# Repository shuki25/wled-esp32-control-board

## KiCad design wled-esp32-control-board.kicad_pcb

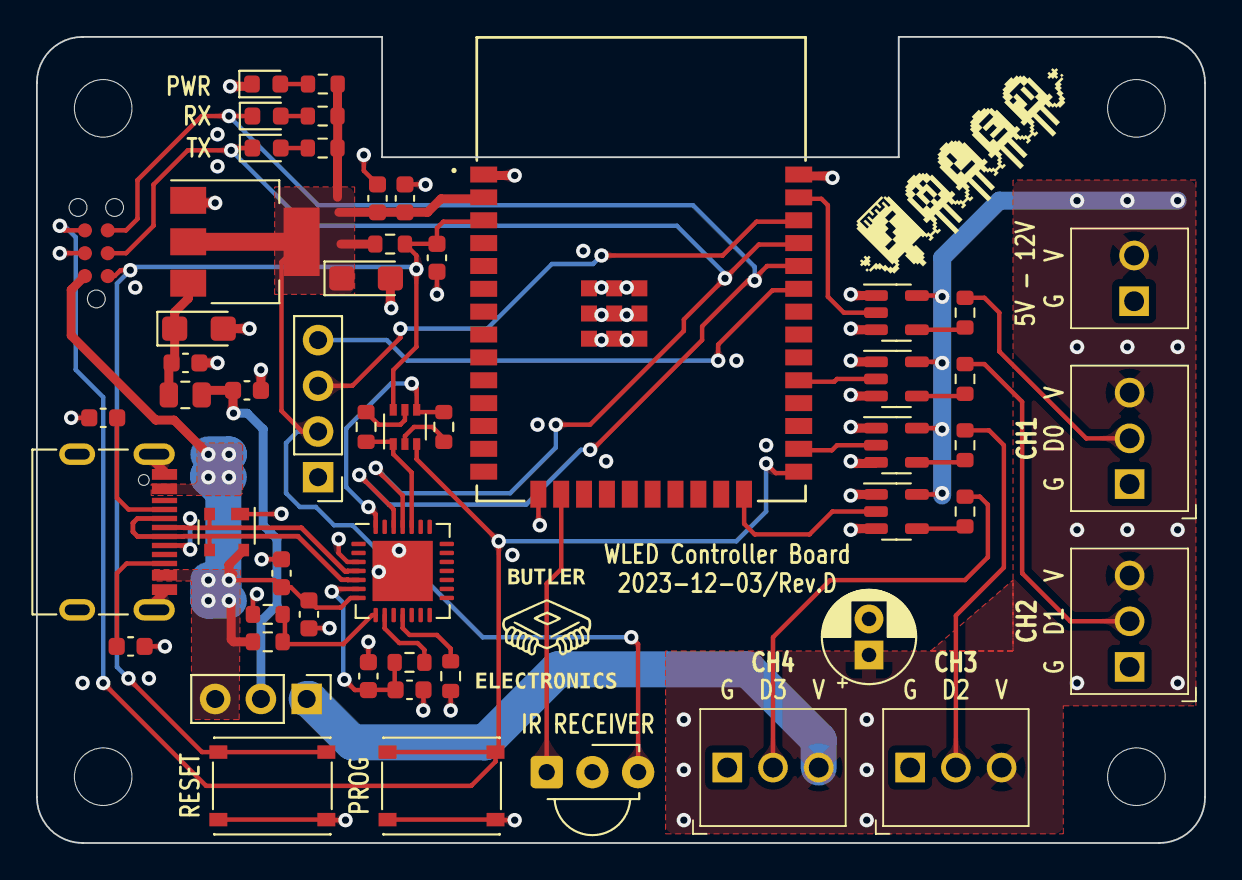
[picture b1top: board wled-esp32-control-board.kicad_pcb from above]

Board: 4 copper layers, 64.9 x 44.8 mm, 57 parts (0 on the bottom side), 40 nets.

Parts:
C101: 22uF; C_0603_1608Metric
C102, C104, C304, C401, C404: 100nF; C_0603_1608Metric
C103: 100uF; CP_Radial_D5.0mm_P2.00mm
C301, C302: 10uF; CP_EIA-3216-10_Kemet-I
C303: 10uF; C_0603_1608Metric
C402, C403: 4.7uF; C_0603_1608Metric
D201: SP0503BAHT; SOT-143
FB301: FerriteBead_Small; R_0805_2012Metric
H101, H102, H103, H104: MountingHole; MountingHole_3.2mm_M3
J101, J102, J103, J104: Conn_01x03; molex-39773-0003
J105: Conn_02x03_Odd_Even; TC2030-IDC-NL
J106: Screw_Terminal_01x02; 397730002
J201: USB_C_Receptacle_USB2.0; USB_C_Receptable_918-418K2023S40001
LED101: BLUE; LED_0603_1608Metric
LED102: GREEN; LED_0603_1608Metric
LED103: RED; LED_0603_1608Metric
OLED101: OLED_I2C; OLED_128x32_I2C_4pins
Q401: MMDT3904; SOT-363_SC-70-6
R101, R402, R405, R408: 10K; R_0603_1608Metric
R102, R103, R106, R108: 100; R_0603_1608Metric
R104, R105, R107: 2K; R_0603_1608Metric
R201, R202: 5K1; C_0603_1608Metric
R401: 1K; R_0603_1608Metric
R403: 22K1; R_0603_1608Metric
R404: 47K5; R_0603_1608Metric
SW101: SW_SPDT; PinHeader_1x03_P2.54mm_Vertical
SW103, SW105: SW_Push; XKB-Connectivity-TS-1187A-B-A-B
U101, U102, U104, U105: 74AHCT1G125; SOT-23-5
U103: ESP32-WROOM-32; ESP32­-WROOM­-32E
U106: TSOP382xx; Vishay_MINICAST-3Pin
U301: LM1117MP-3.3; SOT-223-3_TabPin2
U401: CP2102N-Axx-xQFN28; QFN-28-1EP_5x5mm_P0.5mm_EP3.35x3.35mm

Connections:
+3.3V: C101.1, C102.1, C302.1, OLED101.2 (VCC), R101.1, R104.1, R105.1, R107.1, U103.2 (VDD), U106.3 (Vs), U301.2 (VO)
+5V: C403.1, C404.1, D201.4 (K), J105.2, J201.A4 (VBUS), J201.A9 (VBUS), J201.B4 (VBUS), J201.B9 (VBUS), R403.1, SW101.3 (B), U401.7 (VREGIN)
/CP2102N-AutoProgram/DTR: Q401.4 (E2), R402.2, U401.28 (~DTR)
/CP2102N-AutoProgram/D_N: D201.3 (K), J201.A7 (D-), J201.B7 (D-), U401.5 (D-)
/CP2102N-AutoProgram/D_P: D201.2 (K), J201.A6 (D+), J201.B6 (D+), U401.4 (D+)
/CP2102N-AutoProgram/RTS: Q401.1 (E1), R405.2, U401.24 (~RTS)
/CP2102N-AutoProgram/VDD: C401.1, C402.1, R401.1, U401.6 (VDD)
/EN: C104.1, J105.1, Q401.6 (C1), R101.2, SW103.1, U103.3 (EN)
/ESP_RX: J105.5, LED102.1 (K), U103.34 (RXD0/IO3), U401.26 (TXD)
/ESP_TX: J105.3, LED101.1 (K), U103.35 (TXD0/IO1), U401.25 (RXD)
/IO0: J105.6, Q401.3 (C2), SW105.1, U103.25 (IO0)
/IR_RECV: U103.16 (IO13), U106.1 (OUT)
/LDO/VIN: C303.1, FB301.1, SW101.2 (C)
/LED0: U101.2, U103.37 (IO23)
/LED1: U102.2, U103.29 (IO5)
/LED2: U103.26 (IO4), U104.2
/LED3: U103.24 (IO2), U105.2
/LED_PWR: C103.1, J101.3, J102.3, J103.3, J104.3, J106.2, SW101.1 (A), U101.5 (VCC), U102.5 (VCC), U104.5 (VCC), U105.5 (VCC)
/SCL: OLED101.3 (SCL), U103.36 (IO22)
/SDA: OLED101.4 (SDA), U103.33 (IO21)
GND: C101.2, C102.2, C103.2, C104.2, C301.2, C302.2, C303.2, C304.2, C401.2, C402.2, C403.2, C404.2, D201.1 (A), J101.1, J102.1, J103.1, J104.1, J105.4, J106.1, J201.A1 (GND), J201.A12 (GND), J201.B1 (GND), J201.B12 (GND), J201.S1 (SHIELD), LED103.1 (K), OLED101.1 (GND), R201.1, R202.1, R404.2, R408.2, SW103.2, SW105.2, U101.1, U101.3 (GND), U102.1, U102.3 (GND), U103.1 (GND), U103.15 (GND), U103.38 (GND), U103.39 (GND), U104.1, U104.3 (GND), U105.1, U105.3 (GND), U106.2 (GND), U301.1 (GND), U401.3 (GND), U401.29 (GND)
unnamed: J101.2, R102.2
unnamed: J102.2, R103.2
unnamed: J103.2, R106.2
unnamed: J104.2, R108.2
unnamed: J201.A5 (CC1), R202.2
unnamed: J201.B5 (CC2), R201.2
unnamed: LED101.2 (A), R104.2
unnamed: LED102.2 (A), R105.2
unnamed: LED103.2 (A), R107.2
unnamed: Q401.2 (B1), R402.1
unnamed: Q401.5 (B2), R405.1
unnamed: R102.1, U101.4
unnamed: R103.1, U102.4
unnamed: R106.1, U104.4
unnamed: R108.1, U105.4
unnamed: C301.1, C304.1, FB301.2, U301.3 (VI)
unnamed: R403.2, R404.1, U401.8 (VBUS)
unnamed: R401.2, U401.9 (~RST)
unnamed: R408.1, U401.11 (~SUSPEND)

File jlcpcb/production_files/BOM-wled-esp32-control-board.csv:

Comment,Designator,Footprint,LCSC
100nF,"C102,C104,C202,C401,C402,C403",C_0603_1608Metric,C14663
10uF,C201,C_0805_2012Metric,C15850
4.7uF,C302,C_0603_1608Metric,C19666
100,"R102,R103,R106,R108",R_0603_1608Metric,C22775
RED,LED103,LED_0603_1608Metric,C2286
2K,"R104,R105,R107",R_0603_1608Metric,C22975
5K1,"R201,R202",C_0603_1608Metric,C23186
10K,"R101,R401,R402",R_0603_1608Metric,C25804
Polyfuse_Small,F201,Fuse_0603_1608Metric,C2757930
USB_C_Receptacle_USB2.0,J201,USB_C_Receptable_918-418K2023S40001,C2982555
SW_Push,"SW103,SW105",XKB-Connectivity-TS-1187A-B-A-B,C318884
22uF,"C101,C301",C_0603_1608Metric,C59461
CP2102-GMR,U401,QFN-28-1EP_5x5mm_P0.5mm_EP3.35x3.35mm,C6568
ESP32-WROOM-32,U103,ESP32-WROOM-32,C701341
SP0503BAHT,D201,SOT-143,C7074
BLUE,LED101,LED_0603_1608Metric,C72041
GREEN,LED102,LED_0603_1608Metric,C72043
FerriteBead_Small,FB201,R_0805_2012Metric,C74487
74AHCT1G125,"U101,U102,U104,U105",SOT-23-5,C7484
MMDT3904,Q401,SOT-363_SC-70-6,C83572
XC6220B331MR-G,U301,SOT-23-5,C86534

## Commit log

2023-06-19 update barrel jack
2023-08-12 update settings
2023-08-12 update schematic
2023-08-12 update PCB layout/design
2023-08-12 update production files
2023-08-22 remove caps from tactile button
2023-08-22 reposition cap near EN pin
    Cap repositioned near EN pin. Rev.A does not boot at power on, forcing to press reset button to boot up properly.
    Tactile button caps were removed.
2023-08-22 update silkscreen labels and revision
2023-08-22 update 3d model
2023-10-05 add schematic pdf
2023-10-24 update BOM status
2023-10-24 update DRC exclusions
2023-10-24 update silkscreen and routing
2023-10-29 fix auto-programmer trace
    Fixed a trace that has narrow connection to resistor, not caught by DRC check. Apparently previous iteration was missed, not sure if it's functioning as intended until next production batch.
2023-10-29 bump PCB revision
2023-10-29 update drc exclusion
2023-11-15 fix short traces
2023-11-15 add teardrops
2023-11-15 minor tweaks
    minor tweaks
2023-11-17 update parts
2023-11-17 add mouser part numbers
2023-11-28 add panelization
2023-11-28 update panelization
2023-12-03 update design to replace CP2102 and LDO
2023-12-31 add enclosure STL files
2023-12-31 update stl files
2024-01-01 add fusion 360 files for enclosure
2024-01-11 refactor to accept 12V power
2024-01-15 add origin point for drilling and assembly files
2024-01-15 revise silkscreen text
2024-01-16 update files to KiCad 8 format
